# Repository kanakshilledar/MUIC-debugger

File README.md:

# MUIC debugger for Android Devices

Supports multiple resistance values such as 150k, 523k and 619k. There is also a possibility to place your own resistor.

### Reference
This design is inspired from @anders-bzn/usb-serial-ttl

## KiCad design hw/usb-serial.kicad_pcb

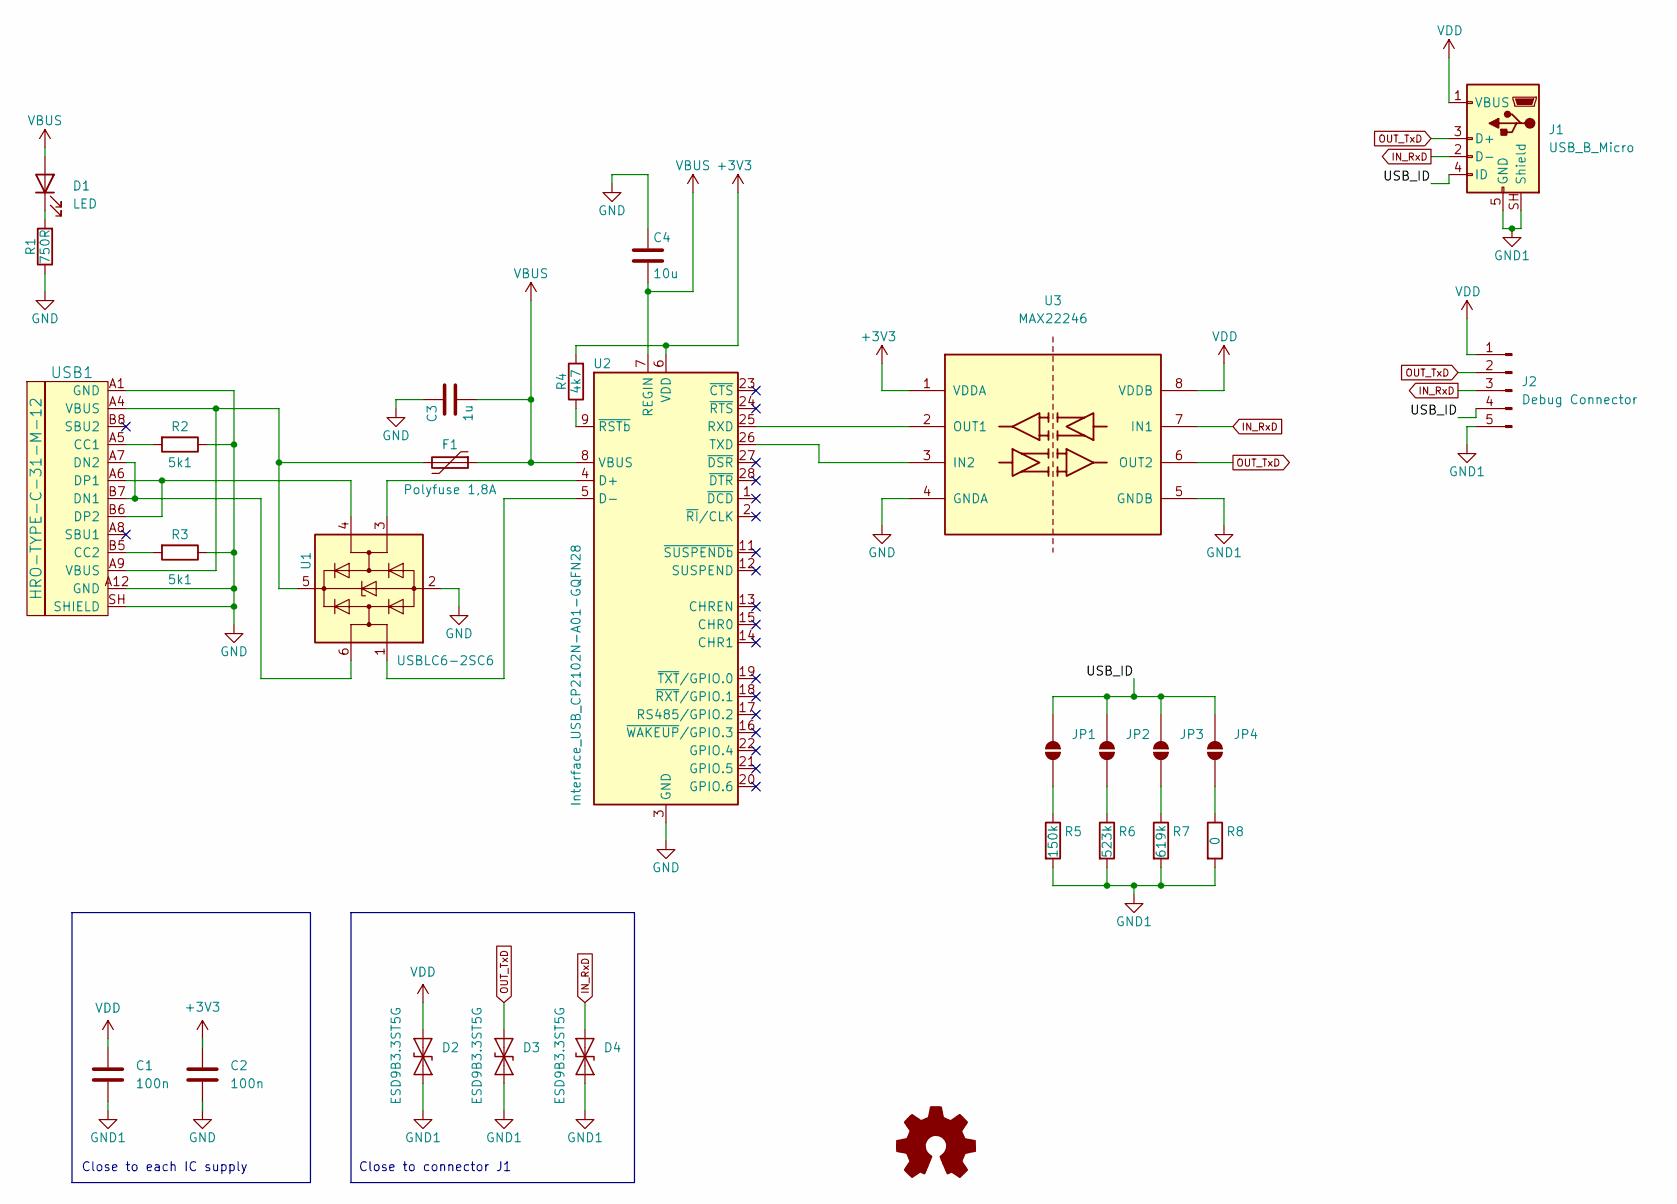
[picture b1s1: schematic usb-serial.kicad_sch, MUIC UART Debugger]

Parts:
C1, C2: 100n; C_0805_2012Metric_Pad1.18x1.45mm_HandSolder
C3: 1u; C_0805_2012Metric_Pad1.18x1.45mm_HandSolder
C4: 10u; C_0805_2012Metric_Pad1.18x1.45mm_HandSolder
D1: LED; LED_0805_2012Metric
D2, D3, D4: ESD9B3.3ST5G; D_SOD-923
F1: Polyfuse 1,8A; Fuse_1206_3216Metric
J1: USB_B_Micro; USB_Micro-B_Amphenol_10118193-0001LF_Horizontal
J2: Debug Connector; PinHeader_1x05_P2.54mm_Vertical
JP1, JP2, JP3, JP4: SolderJumper_2_Open; SolderJumper-2_P1.3mm_Open_TrianglePad1.0x1.5mm
R1: 750R; R_0805_2012Metric_Pad1.20x1.40mm_HandSolder
R2, R3: 5k1; R_0402_1005Metric
R4: 4k7; R_0805_2012Metric_Pad1.20x1.40mm_HandSolder
R5: 150k; R_0805_2012Metric_Pad1.20x1.40mm_HandSolder
R6: 523k; R_0805_2012Metric_Pad1.20x1.40mm_HandSolder
R7: 619k; R_0805_2012Metric_Pad1.20x1.40mm_HandSolder
R8: 0; R_0805_2012Metric_Pad1.20x1.40mm_HandSolder
U1: USBLC6-2SC6; SOT-23-6
U2: Interface_USB_CP2102N-A01-GQFN28; QFN-28-1EP_5x5mm_P0.5mm_EP3.35x3.35mm
U3: MAX22246; SOIC-8_7.5x5.85mm_P1.27mm
USB1: HRO-TYPE-C-31-M-12; USB_C_Receptacle_HCTL_HC-TYPE-C-16P-01A

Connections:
+3V3: C2.1, R4.2, U2.6 (VDD), U3.1 (VDDA)
/USB_ID: J1.4 (ID), J2.4, JP1.2 (B), JP2.2 (B), JP3.2 (B), JP4.2 (B)
GND: C2.2, C3.1, C4.1, R1.1, R2.1, R3.1, U1.2 (GND), U2.3 (GND), U2.29 (GND), U3.4 (GNDA), USB1.A1 (GND), USB1.A12 (GND), USB1.SH (SHIELD)
GND1: C1.2, D2.1 (A1), D3.1 (A1), D4.1 (A1), J1.5 (GND), J1.SH (Shield), J2.5, R5.2, R6.2, R7.2, R8.2, U3.5 (GNDB)
IN_RxD: D4.2 (A2), J1.2 (D-), J2.3, U3.7 (IN1)
unnamed: D1.1 (K), R1.2
unnamed: JP1.1 (A), R5.1
unnamed: JP2.1 (A), R6.1
unnamed: JP3.1 (A), R7.1
unnamed: JP4.1 (A), R8.1
unnamed: F1.2, U1.5 (VBUS), USB1.A4 (VBUS), USB1.A9 (VBUS)
unnamed: U1.3 (I/O2), U2.4 (D+)
unnamed: U1.1 (I/O1), U2.5 (D-)
unnamed: U2.25 (RXD), U3.2 (OUT1)
unnamed: U2.26 (TXD), U3.3 (IN2)
unnamed: R4.1, U2.9 (~RSTb)
unnamed: R2.2, USB1.A5 (CC1)
unnamed: R3.2, USB1.B5 (CC2)
unnamed: U1.6 (I/O1), USB1.A7 (DN2), USB1.B7 (DN1)
unnamed: U1.4 (I/O2), USB1.A6 (DP1), USB1.B6 (DP2)
OUT_TxD: D3.2 (A2), J1.3 (D+), J2.2, U3.6 (OUT2)
VBUS: C3.2, C4.2, D1.2 (A), F1.1, U2.7 (REGIN), U2.8 (VBUS)
VDD: C1.1, D2.2 (A2), J1.1 (VBUS), J2.1, U3.8 (VDDB)

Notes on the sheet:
Close to each IC supply
Close to connector J1

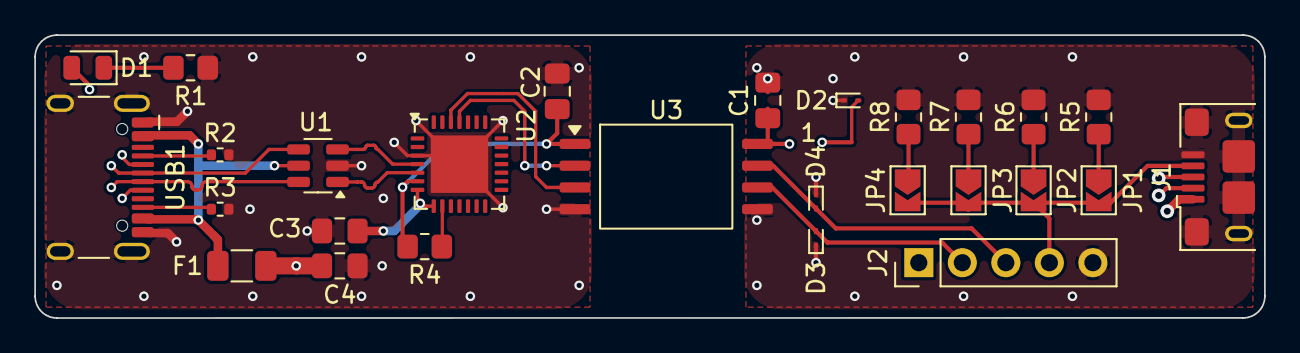
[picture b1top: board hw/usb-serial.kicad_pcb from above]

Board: 4 copper layers, 71.8 x 16.5 mm, 27 parts (0 on the bottom side), 23 nets.

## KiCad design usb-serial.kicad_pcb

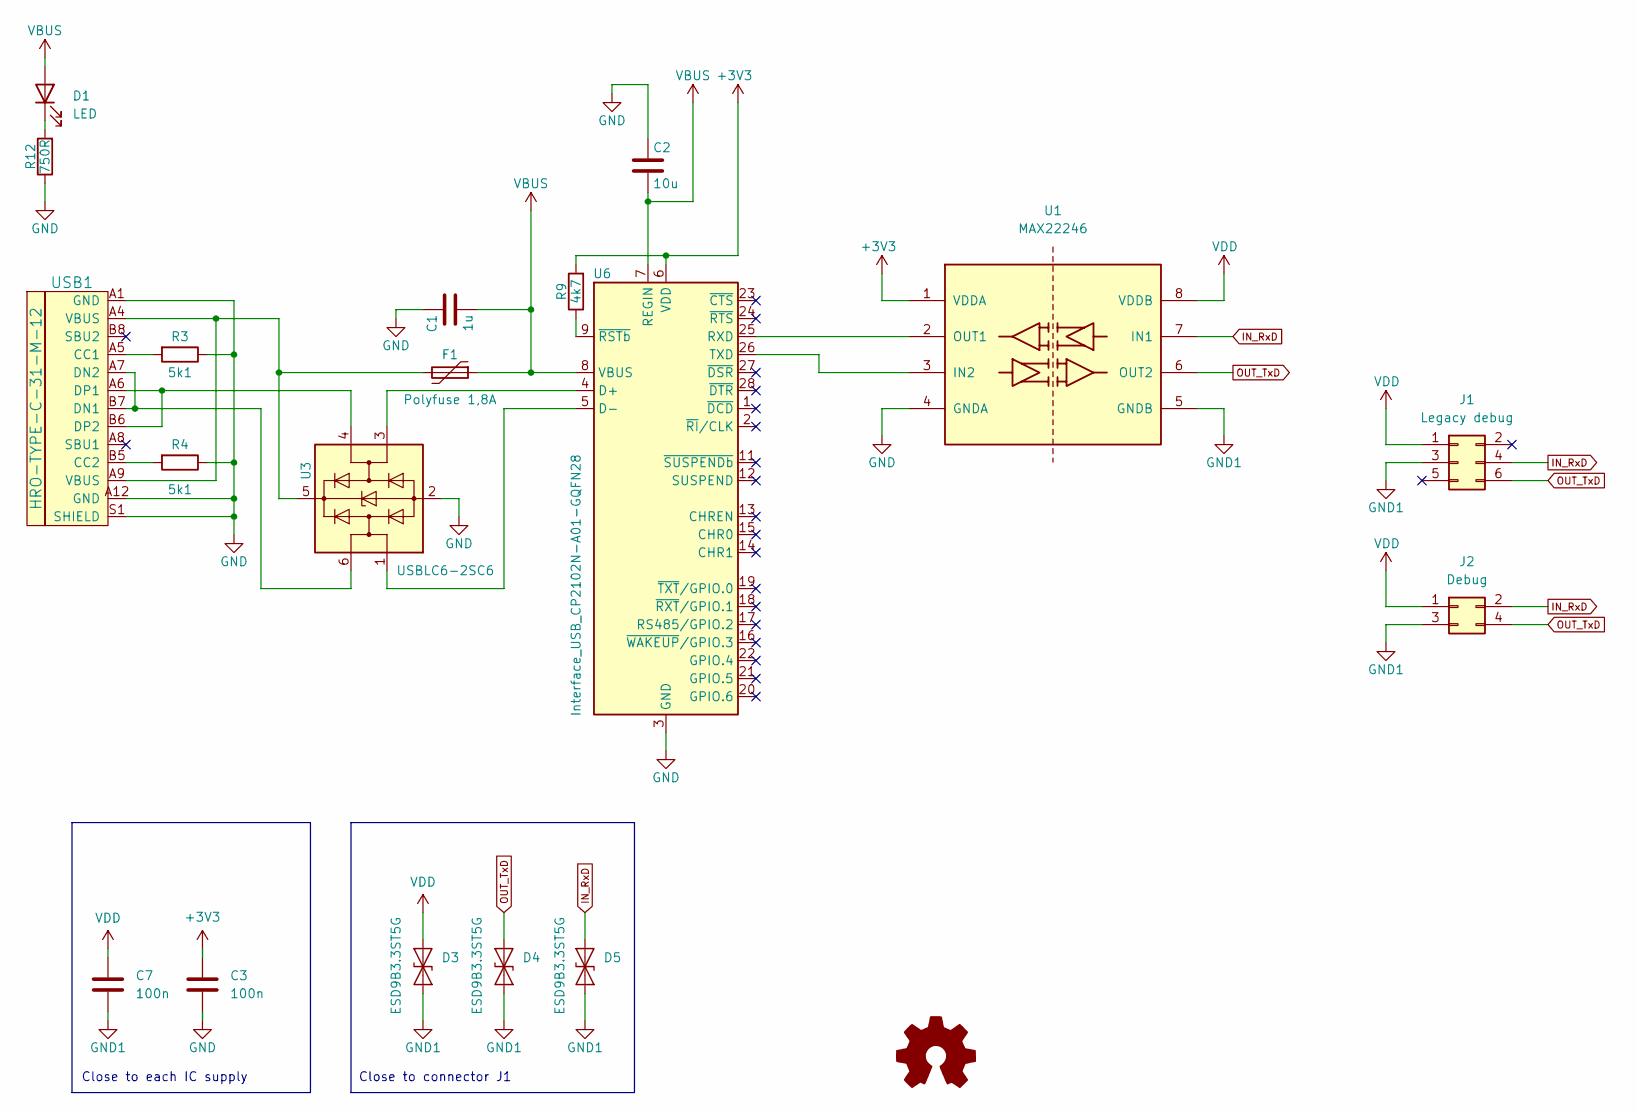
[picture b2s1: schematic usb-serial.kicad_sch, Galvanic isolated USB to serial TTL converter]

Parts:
C1: 1u; C_0805_2012Metric
C2: 10u; C_0805_2012Metric
C3, C7: 100n; C_0402_1005Metric
D1: LED; LED_0805_2012Metric
D3, D4, D5: ESD9B3.3ST5G; D_SOD-923
F1: Polyfuse 1,8A; Fuse_1206_3216Metric
J1: Legacy debug; PinHeader_2x03_P2.00mm_Vertical_SMD
J2: Debug; JST_PH_S4B-PH-SM4-TB_1x04-1MP_P2.00mm_Horizontal
R3, R4: 5k1; R_0402_1005Metric
R9: 4k7; R_0402_1005Metric
R12: 750R; R_0402_1005Metric
U1: MAX22246
U3: USBLC6-2SC6; SOT-23-6
U6: Interface_USB_CP2102N-A01-GQFN28; QFN-28-1EP_5x5mm_P0.5mm_EP3.35x3.35mm
USB1: HRO-TYPE-C-31-M-12; USB_C_Receptacle_HRO_TYPE-C-31-M-12

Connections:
+3V3: C3.1, R9.2, U1.1 (VDDA), U6.6 (VDD)
GND: C1.1, C2.1, C3.2, R3.1, R4.1, R12.1, U1.4 (GNDA), U3.2 (GND), U6.3 (GND), U6.29 (GND), USB1.A1 (GND), USB1.A12 (GND), USB1.S1 (SHIELD)
GND1: C7.2, D3.1 (A1), D4.1 (A1), D5.1 (A1), J1.3, J2.3, U1.5 (GNDB)
IN_RxD: D5.2 (A2), J1.4, J2.2, U1.7 (IN1)
unnamed: D1.1 (K), R12.2
unnamed: U1.3 (IN2), U6.26 (TXD)
unnamed: U1.2 (OUT1), U6.25 (RXD)
unnamed: F1.2, U3.5 (VBUS), USB1.A4 (VBUS), USB1.A9 (VBUS)
unnamed: U3.3 (I/O2), U6.4 (D+)
unnamed: U3.1 (I/O1), U6.5 (D-)
unnamed: R9.1, U6.9 (~RSTb)
unnamed: R3.2, USB1.A5 (CC1)
unnamed: R4.2, USB1.B5 (CC2)
unnamed: U3.6 (I/O1), USB1.A7 (DN2), USB1.B7 (DN1)
unnamed: U3.4 (I/O2), USB1.A6 (DP1), USB1.B6 (DP2)
OUT_TxD: D4.2 (A2), J1.6, J2.4, U1.6 (OUT2)
VBUS: C1.2, C2.2, D1.2 (A), F1.1, U6.7 (REGIN), U6.8 (VBUS)
VDD: C7.1, D3.2 (A2), J1.1, J2.1, U1.8 (VDDB)

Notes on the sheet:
Close to each IC supply
Close to connector J1

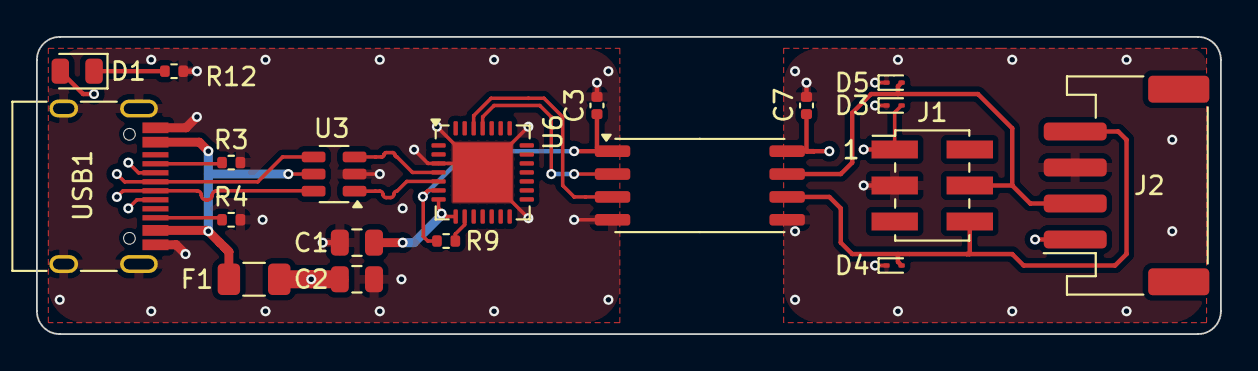
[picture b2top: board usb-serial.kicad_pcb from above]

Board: 4 copper layers, 65.8 x 16.5 mm, 19 parts (0 on the bottom side), 18 nets.

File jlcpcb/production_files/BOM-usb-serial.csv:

Comment,Designator,Footprint,LCSC,Quantity
4k7,R9,R_0402_1005Metric,C105870,1
5k1,"R3,R4",R_0402_1005Metric,C105872,2
10u,C2,C_0805_2012Metric,C15850,1
HRO-TYPE-C-31-M-12,USB1,USB_C_Receptacle_HRO_TYPE-C-31-M-12,C165948,1
Debug,J2,JST_PH_S4B-PH-SM4-TB_1x04-1MP_P2.00mm_Horizontal,C265102,1
1u,C1,C_0805_2012Metric,C28323,1
LED,D1,LED_0805_2012Metric,C2971980,1
100n,"C3,C7",C_0402_1005Metric,C307331,2
"Polyfuse 1,8A",F1,Fuse_1206_3216Metric,C70081,1
MAX22246,U1,MAX22246,C7452984,1
USBLC6-2SC6,U3,SOT-23-6,C7519,1
750R,R12,R_0402_1005Metric,C881134,1
Interface_USB_CP2102N-A01-GQFN28,U6,QFN-28-1EP_5x5mm_P0.5mm_EP3.35x3.35mm,C964632,1
ESD9B3.3ST5G,"D3,D4,D5",D_SOD-923,C96512,3

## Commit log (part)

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2025-01-16 Corrected U1 footprint
